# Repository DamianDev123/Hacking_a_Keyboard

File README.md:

# Hacking_a_Keyboard

Hacking_a_Keyboard is a 9 key macropad with a OLED display, and WS2812B LEDs. It runs KMK firmware.

---

## Features:
- 128×32 OLED display
- 4× WS2812B RGB LEDs
- 9 keys
---

## CAD Model:
Everything fits together using 6 M3 bolts and heat-set inserts:
- 4 for the case
- 2 for securing the PCB

It consists of 3 printed parts:
- Bottom case
- Top cover

Made in Onshape.

---

## PCB:
Designed in KiCad with silkscreen imported from Figma.

Schematic:

PCB:

---

## Firmware Overview:
This hackpad uses KMK firmware.

- 9 keys:
  - randoms keys

- RGB:
  - Gaming
    
- OLED display:
  - TODO

More features may be added later.

---

## BOM:
Everything needed to build the hackpad:

- 9× Cherry MX switches
- 9× DSA keycaps
- 4× M3×5×4 heat-set inserts
- 6× M3×16 SHCS bolts
- 9× 1N4148 DO-35 diodes
- 4× WS2812B LEDs
- 1× 0.91" 128×32 OLED display
- 1× Seeed XIAO RP2040
- 1× case (2 printed parts)

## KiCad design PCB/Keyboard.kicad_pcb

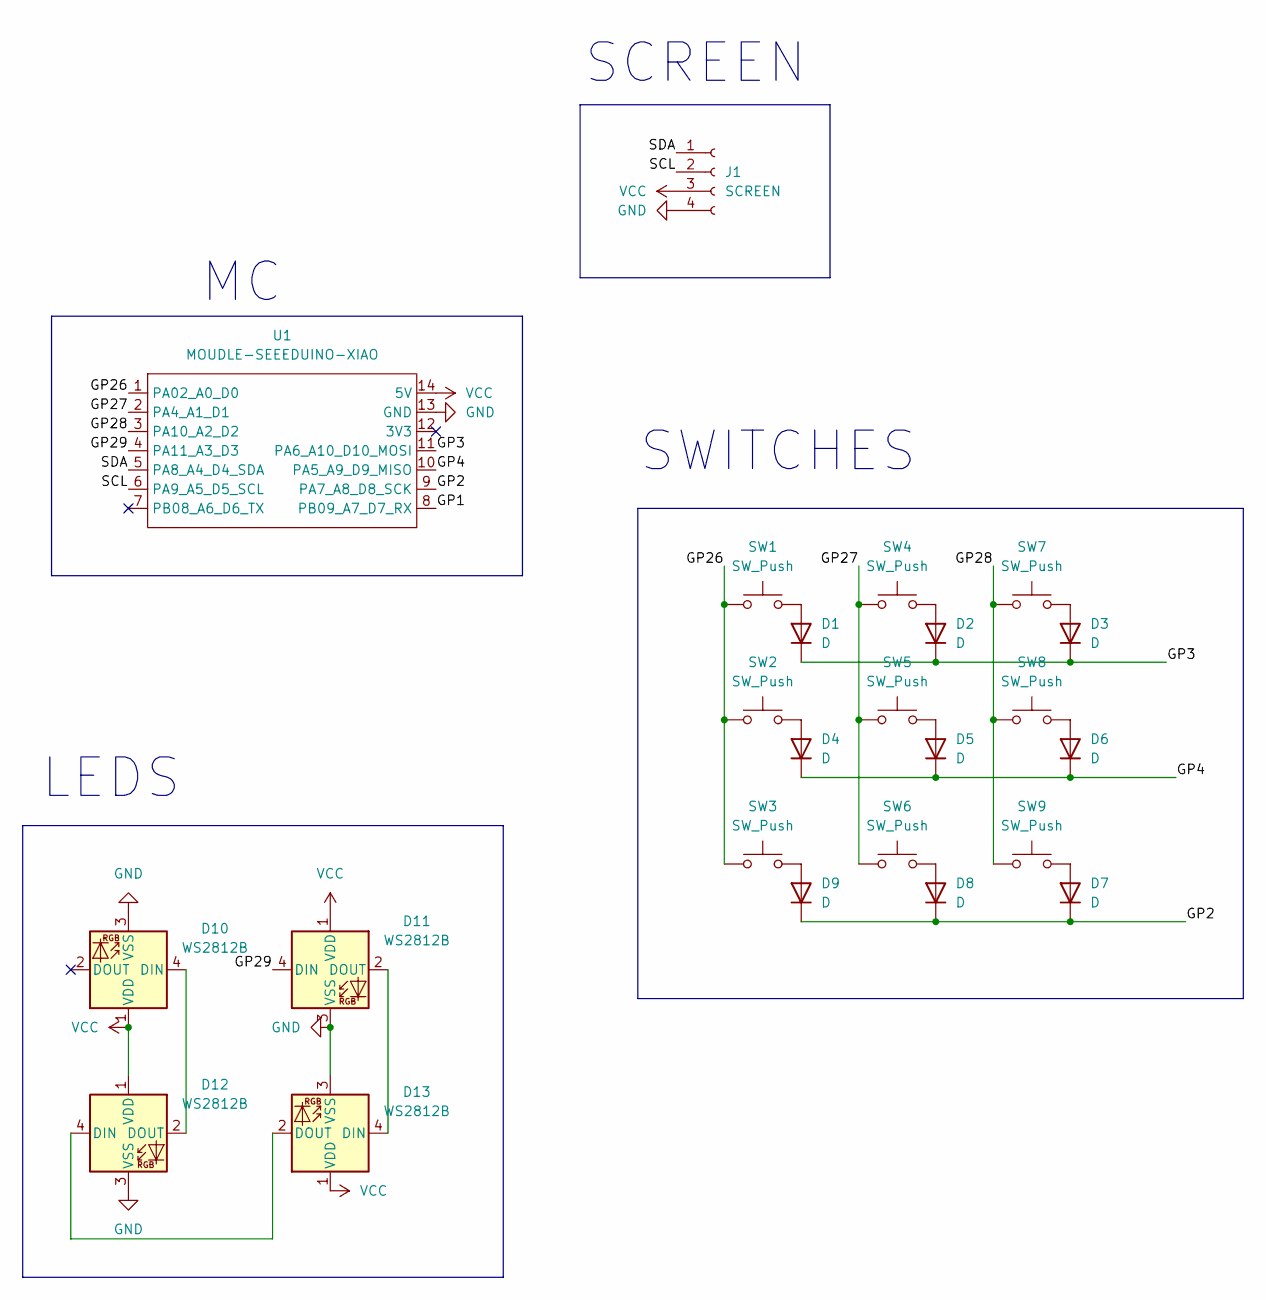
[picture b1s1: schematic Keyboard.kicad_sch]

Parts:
D1, D2, D3, D4, D5, D6, D7, D8, D9: D; D_DO-35_SOD27_P7.62mm_Horizontal
D10, D11, D12, D13: WS2812B; SK6812MINI-E_fixed
J1: SCREEN; PinSocket_1x04_P2.54mm_Vertical
SW1, SW2, SW3, SW4, SW5, SW6, SW7, SW8, SW9: SW_Push; SW_Cherry_MX_1.00u_PCB
U1: MOUDLE-SEEEDUINO-XIAO; XIAO-Generic-Hybrid-14P-2.54-21X17.8MM

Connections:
/GP1: U1.8 (PB09_A7_D7_RX)
/GP2: D7.1 (K), D8.1 (K), D9.1 (K), U1.9 (PA7_A8_D8_SCK)
/GP3: D1.1 (K), D2.1 (K), D3.1 (K), U1.11 (PA6_A10_D10_MOSI)
/GP4: D4.1 (K), D5.1 (K), D6.1 (K), U1.10 (PA5_A9_D9_MISO)
/GP26: SW1.1, SW2.1, SW3.1, U1.1 (PA02_A0_D0)
/GP27: SW4.1, SW5.1, SW6.1, U1.2 (PA4_A1_D1)
/GP28: SW7.1, SW8.1, SW9.1, U1.3 (PA10_A2_D2)
/GP29: D11.4 (DIN), U1.4 (PA11_A3_D3)
/SCL: J1.2, U1.6 (PA9_A5_D5_SCL)
/SDA: J1.1, U1.5 (PA8_A4_D4_SDA)
GND: D10.3 (VSS), D11.3 (VSS), D12.3 (VSS), D13.3 (VSS), J1.4, U1.13 (GND)
unnamed: D1.2 (A), SW1.2
unnamed: D2.2 (A), SW4.2
unnamed: D3.2 (A), SW7.2
unnamed: D4.2 (A), SW2.2
unnamed: D5.2 (A), SW5.2
unnamed: D6.2 (A), SW8.2
unnamed: D7.2 (A), SW9.2
unnamed: D8.2 (A), SW6.2
unnamed: D9.2 (A), SW3.2
unnamed: D10.4 (DIN), D12.2 (DOUT)
unnamed: D11.2 (DOUT), D13.4 (DIN)
unnamed: D12.4 (DIN), D13.2 (DOUT)
VCC: D10.1 (VDD), D11.1 (VDD), D12.1 (VDD), D13.1 (VDD), J1.3, U1.14 (5V)

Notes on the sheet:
LEDS
SCREEN
SWITCHES

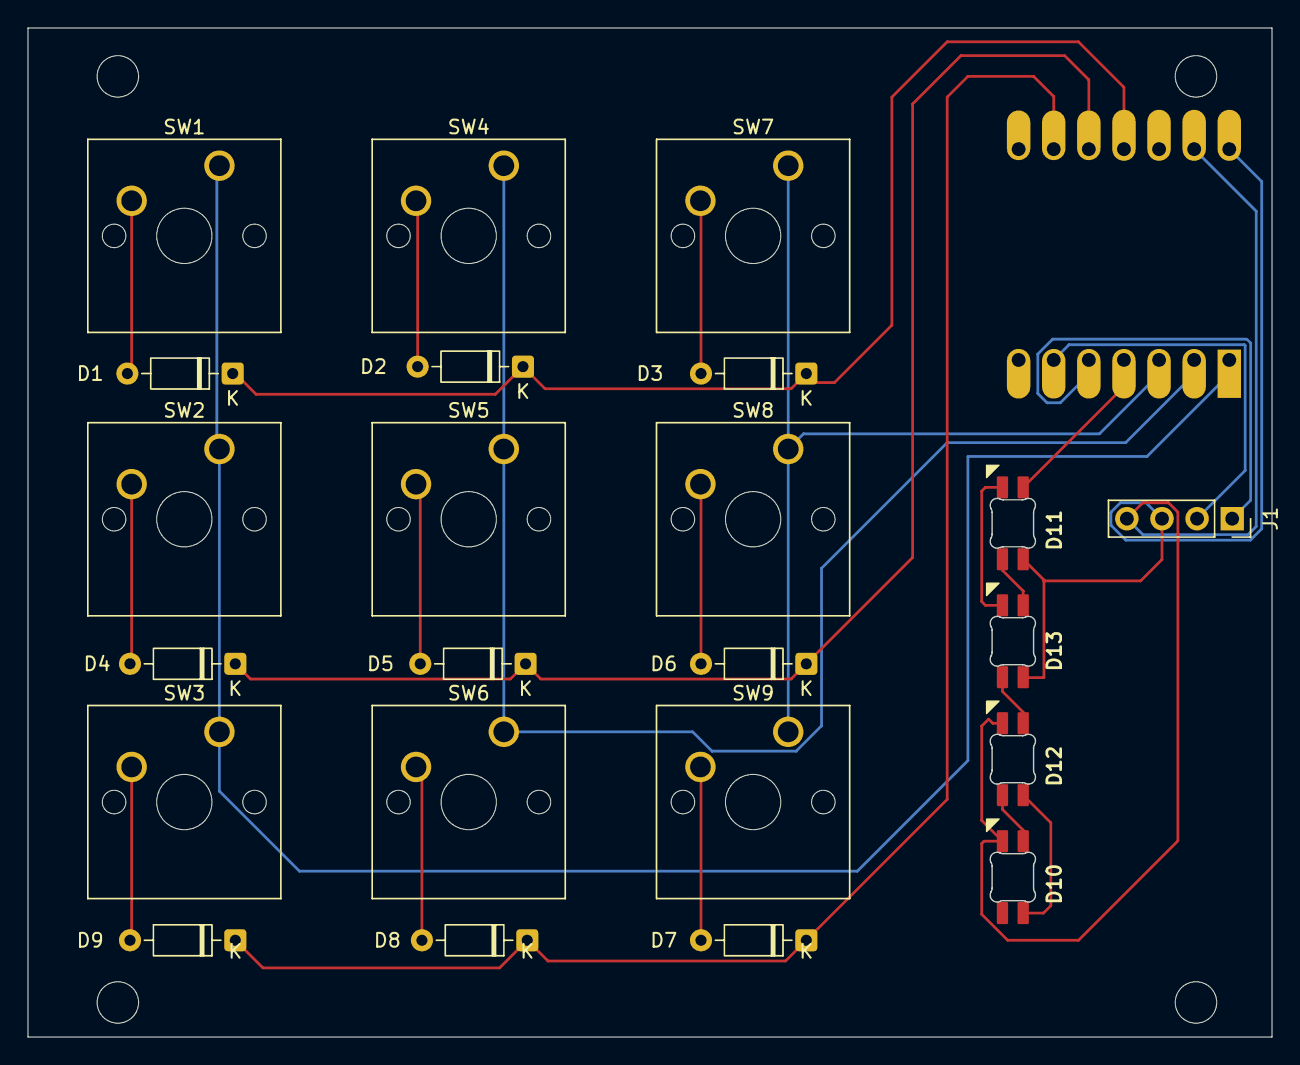
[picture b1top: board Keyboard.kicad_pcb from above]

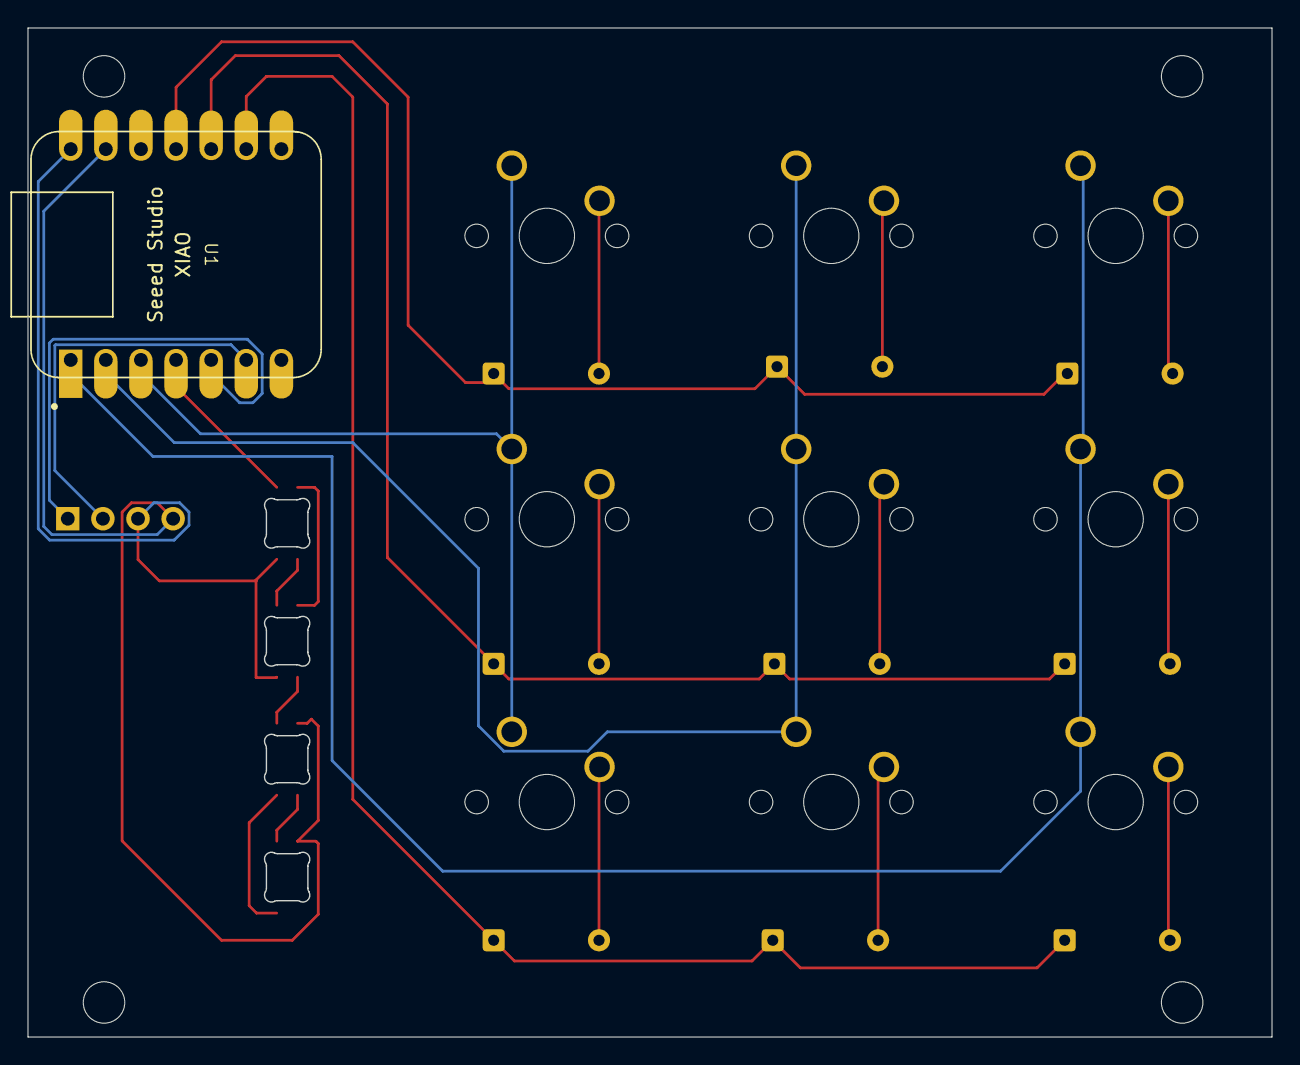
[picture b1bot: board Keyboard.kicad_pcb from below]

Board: 2 copper layers, 90.0 x 73.0 mm, 24 parts (5 on the bottom side), 23 nets.

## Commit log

2026-06-22 Readme Update
2026-06-29 Ipdate
2026-06-29 Revise README with Orpheuspad specificationsR
    Updated README to include details about Orpheuspad, its features, CAD model, PCB design, firmware overview, and BOM.
2026-06-29 Adjust PCB image size in README
    Updated PCB image dimensions in README.md.
2026-06-29 Rename project to Hacking_a_Keyboard
    Updated project name and description in README.
